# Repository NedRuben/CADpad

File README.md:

# CADpad
CADpad is a hackpad wich is most suited for CAD and video editing.

# Obstacles
During the setup of Kicad, I had some difficulties with the conponent footprints, but after that, it was smooth sailing.

# BOM
- 1x XIAO RP2040
- 6x Cherry MX Switches
- 6x Blank DSA Keycaps
- 4x SK6812 MINI Leds
- 4x M3x16 Bolt
- 4x M3 Heatset

# 3d printed parts
- Base
- Top

# others
- The firmware
- And lastly the pcb

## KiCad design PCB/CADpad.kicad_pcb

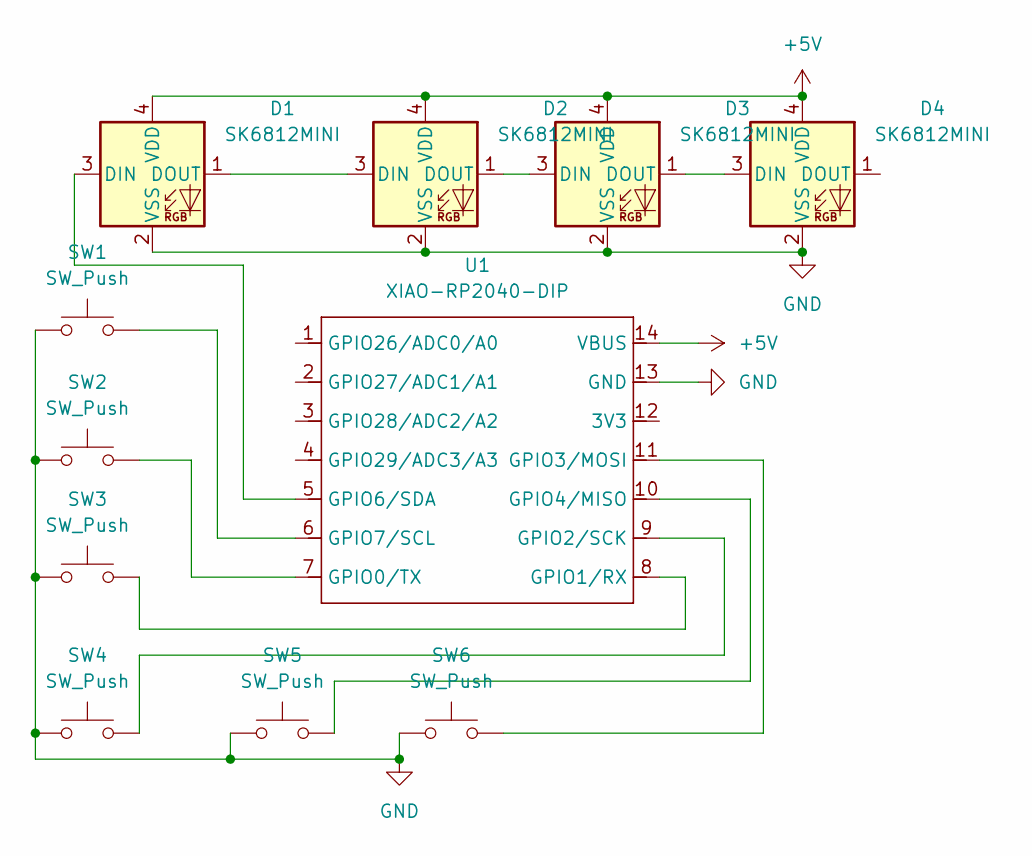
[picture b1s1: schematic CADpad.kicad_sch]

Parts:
D1, D2, D3, D4: SK6812MINI; LED_SK6812MINI_PLCC4_3.5x3.5mm_P1.75mm
SW1, SW2, SW3, SW4, SW5, SW6: SW_Push; SW_Cherry_MX_1.00u_PCB
U1: XIAO-RP2040-DIP

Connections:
+5V: D1.4 (VDD), D2.4 (VDD), D3.4 (VDD), D4.4 (VDD), U1.14 (VBUS)
GND: D1.2 (VSS), D2.2 (VSS), D3.2 (VSS), D4.2 (VSS), SW1.1, SW2.1, SW3.1, SW4.1, SW5.1, SW6.1, U1.13 (GND)
unnamed: D1.3 (DIN), U1.5 (GPIO6/SDA)
unnamed: D1.1 (DOUT), D2.3 (DIN)
unnamed: D2.1 (DOUT), D3.3 (DIN)
unnamed: D3.1 (DOUT), D4.3 (DIN)
unnamed: SW2.2, U1.7 (GPIO0/TX)
unnamed: SW3.2, U1.8 (GPIO1/RX)
unnamed: SW4.2, U1.9 (GPIO2/SCK)
unnamed: SW6.2, U1.11 (GPIO3/MOSI)
unnamed: SW5.2, U1.10 (GPIO4/MISO)
unnamed: SW1.2, U1.6 (GPIO7/SCL)

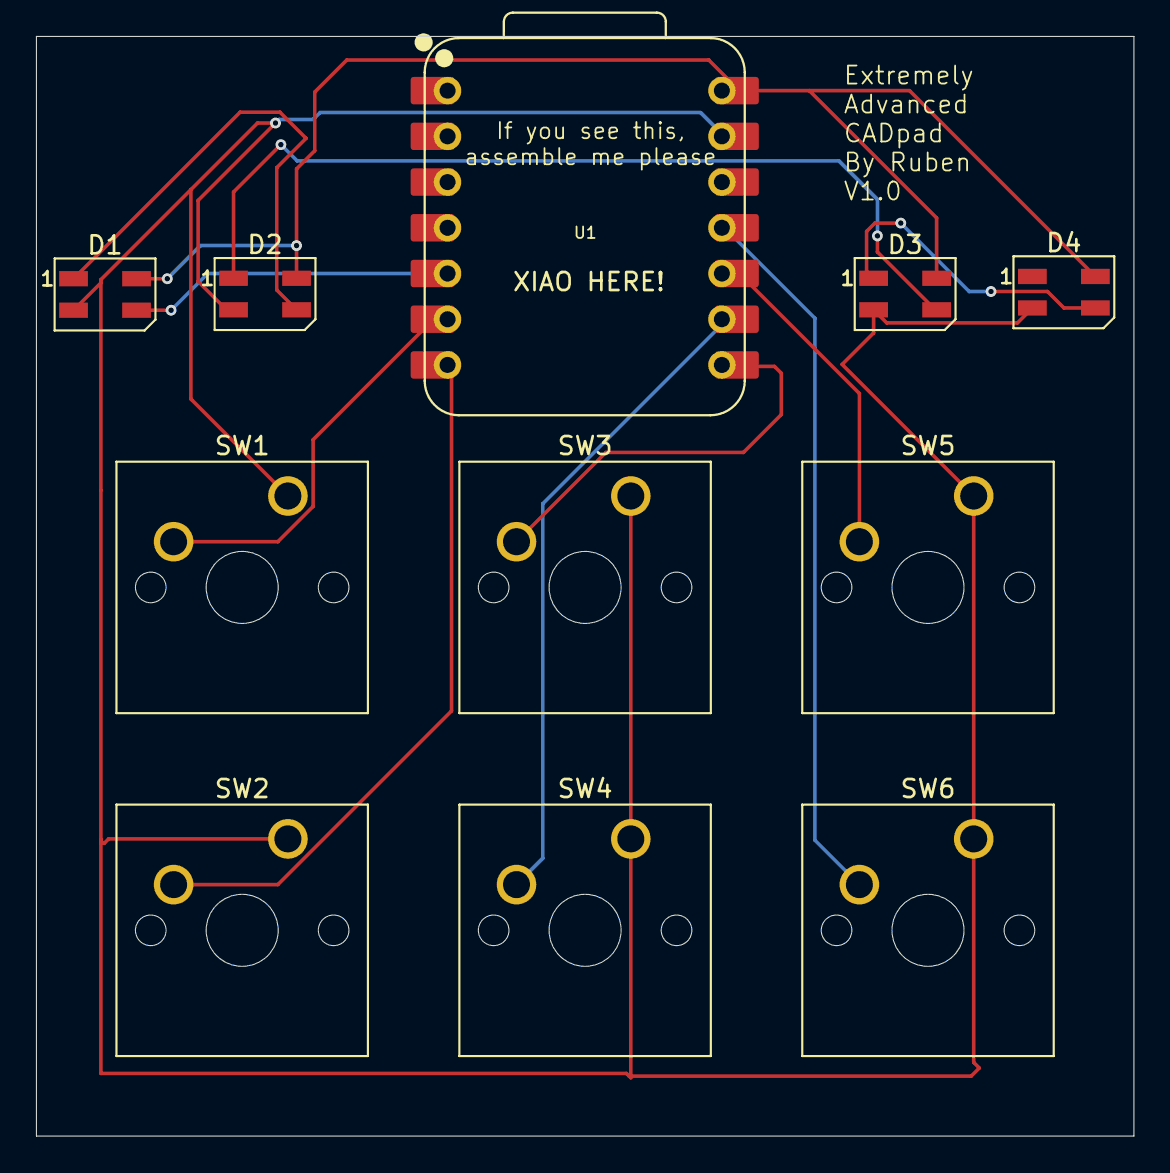
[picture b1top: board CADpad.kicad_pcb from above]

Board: 2 copper layers, 61.0 x 61.1 mm, 11 parts (0 on the bottom side), 12 nets.

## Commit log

2025-12-16 Create main body
2025-12-16 Added files
2025-12-16 Files added
2025-12-16 Create pcb
2025-12-16 Create FIRMWARE
